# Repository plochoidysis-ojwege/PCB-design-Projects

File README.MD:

# PCB Design Projects

I created this repository to document my learning journey with KiCad and to share my designs with others. My goal is to create a comprehensive resource for anyone looking to get started with PCB design using KiCad and also as a personal reference for my future projects.
The structure of this repository is as follows:
1. [Learning and Desmistifying KiCad first directory](https://github.com/plochoidysis-ojwege/PCB-design-Projects/tree/main/Learning%20and%20desmistifyng%20KiCad%20first)  - here , I use tutorials and examples to learn the basics of KiCad and PCB design.
2. [My original designs directory](https://github.com/plochoidysis-ojwege/PCB-design-Projects/tree/main/My%20original%20designs) - here, I apply what I've learned in more advanced projects and explore additional features of KiCad.
3. [Documentation](https://github.com/plochoidysis-ojwege/PCB-design-Projects/tree/main/Documentation)-of essence, each project has its own documentation folder in its directory, so this directory has two files :
   - [Glossary of KiCad terms.md](https://github.com/plochoidysis-ojwege/PCB-design-Projects/blob/main/Documentation/Glossary%20of%20KiCad%20terms.MD) - here, I define key terms and concepts related to KiCad and PCB design.
   - [Important links.md](https://github.com/plochoidysis-ojwege/PCB-design-Projects/blob/main/Documentation/Important%20links.md) - here, I keep links to all the documentation related to my projects, including design notes, tutorials, and references, but of essence, each project has its own documentation folder in its directory.
   * Note that:
- Each project is contained within its own directory
- Each project directory includes the KiCad project files, as well as any relevant documentation
- The README.md file in each project directory provides an overview of the project and its goals.

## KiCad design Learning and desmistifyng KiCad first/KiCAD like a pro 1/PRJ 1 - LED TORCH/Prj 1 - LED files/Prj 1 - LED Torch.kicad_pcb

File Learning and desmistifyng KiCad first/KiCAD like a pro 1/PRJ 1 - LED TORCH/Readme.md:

# LED Torch Project
This is my first project using KiCad. The goal is to design a simple LED torch circuit and overally to learn the basics of KiCad, including schematic capture and PCB layout.
## Components
- 1 x LED
- 1 x Resistor
- 1 x  Battery
- 1 x Battery Clip
- 1 x Switch

## Schematic
Below is a simple schematic representation of the LED torch circuit:

From this schematic, I learnt the following features of KiCad:
- How to set up a new project and configure the environment(including grid settings)
- How to place components on the schematic
- How to wire components together
- How to annotate the schematic
- How to run electrical rules checks (ERC)

The problem and I still haven't figured out is whether the warning about the unplaced unit is something I need to address before moving on to the PCB layout.Is it that big deal. In this case , the sinlge pole switch had unplaced unit B as shown below :

but , it's the beginning and I have time to figure it out.

## PCB Layout
Below is the PCB layout for the LED torch circuit:

From this layout, I learnt the following features of KiCad:
- How to import the schematic into the PCB layout
- How to place components on the PCB
- How to route traces between components
- How to define board edges and cutouts
- How to run DRC(Design rules checks)
- How to generate [Gerber files](https://github.com/plochoidysis-ojwege/PCB-design-Projects/tree/main/Learning%20and%20desmistifyng%20KiCad%20first/KiCAD%20like%20a%20pro%201/PRJ%201%20-%20LED%20TORCH/Prj%201%20-%20LED%20%20files/Gerber%20files%20for%20this%20project) for manufacturing.
  
  Below is the design rules check;

The thing I found challenging was the routing process, especially ensuring that all traces were properly connected and that there were no unintentional shorts. Again here I realised their is a minimum distance between traces that I need to adhere to.

The PCB layout process was quite intuitive, and I appreciate the visual feedback KiCad provides while routing traces. I still need to learn more about design rules and how to ensure my layout is manufacturable, but I'm excited to continue this journey.
Below is a 3D view of the PCB layout:

Here is the back view;

I have included the files for this project -
[HERE](https://github.com/plochoidysis-ojwege/PCB-design-Projects/tree/main/Learning%20and%20desmistifyng%20KiCad%20first/KiCAD%20like%20a%20pro%201/PRJ%201%20-%20LED%20TORCH/Prj%201%20-%20LED%20%20files)

---
THE END

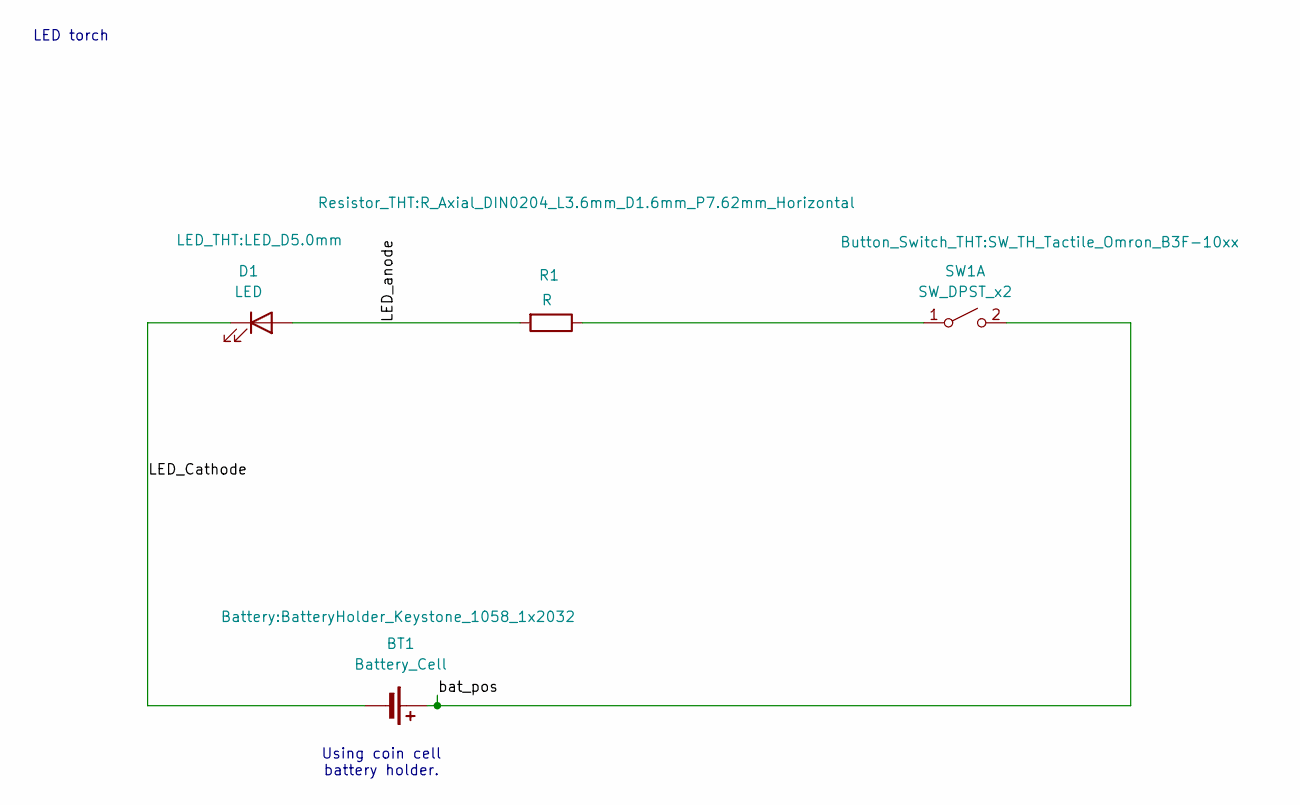
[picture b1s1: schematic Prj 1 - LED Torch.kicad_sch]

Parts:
BT1: Battery_Cell; BatteryHolder_Keystone_1058_1x2032
D1: LED; LED_D5.0mm
R1: R; R_Axial_DIN0204_L3.6mm_D1.6mm_P7.62mm_Horizontal
SW1: SW_DPST_x2; SW_TH_Tactile_Omron_B3F-10xx

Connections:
/LED_Cathode: BT1.2 (-), D1.1 (K)
/LED_anode: D1.2 (A), R1.2
/bat_pos: BT1.1 (+), SW1.2 (B)
unnamed: R1.1, SW1.1 (A)

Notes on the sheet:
Using coin cell battery holder.
LED torch

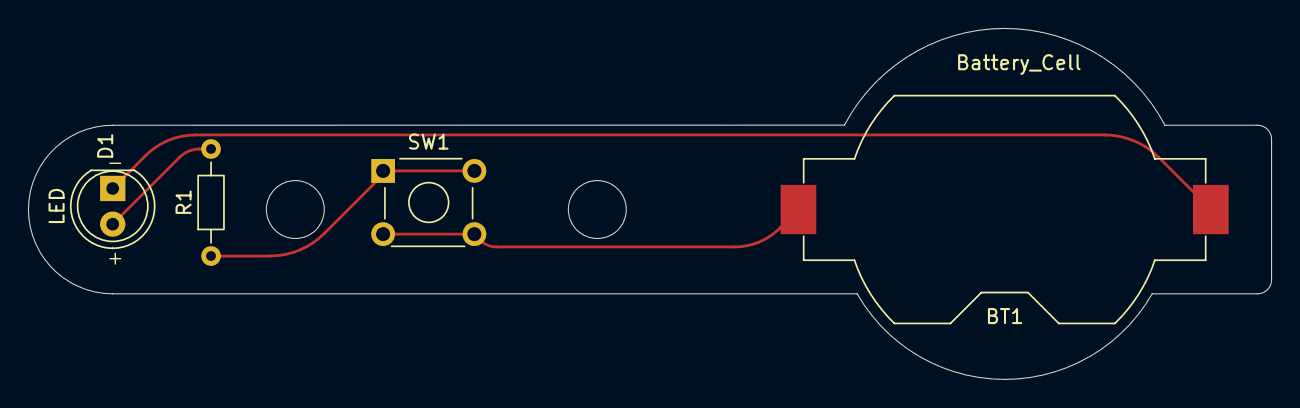
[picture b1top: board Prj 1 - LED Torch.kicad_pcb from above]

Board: 2 copper layers, 88.5 x 25.0 mm, 5 parts (1 on the bottom side), 4 nets.

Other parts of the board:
REF1: KiCad-Logo2_8mm_SilkScreen

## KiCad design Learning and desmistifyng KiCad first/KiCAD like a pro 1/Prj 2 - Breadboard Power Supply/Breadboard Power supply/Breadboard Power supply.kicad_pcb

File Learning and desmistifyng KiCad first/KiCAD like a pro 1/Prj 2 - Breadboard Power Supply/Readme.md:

# Breadboard Power supply
## Overview
This is the second project I've done.It was inspired by the project in the book "Kicad like a pro" by Peter Dalmaris under a chapter called "Part 9:Project-Design a simple breadboard power supply PCB".This was a project to design a simple breadboard power supply PCB,to provide power to circuits implemented on a mini breadboard, which is a core part of electronics prototyping.The inspiration for the design of the PCB came from creating small eletronics for his(Peter Dalmaris') Arduino and ESP32 courses. When the circuit he was building on the breadboard needed more power than the MCU could provide, he settled on this project.

 For the breadboard power supply,we needed something that:
 1. Plugs directly on the breadboard;therefore, there are no wires.
 2. Have an on/off switch.
 3. Can provide 5V and 3.3V power.
 4. Can draw power from a range of wall power supplies,from 6V to 12V.

 The breadboard connects to the PCB through two sets of pin headers.Two double screw terminals are added to provide additional way to output power via jumper wires instead pins.

 From this project I learnt the following: 
 - How to import and use footprints and parts from external libraries.
 - How to use vias in routing to connect the B.copper to F.copper routes.
 - How to use copper fills and their importance.

 And other things, I already learnt them in other subsequent projects or I'm yet to.
 ## Bill of Materials
 Here is the generated B.O.M
 
 This was not the bill of materials used in KiCad like a pro,I used my own switch instead of the digikey one used in the book.And also assigned a footprint that is compartible as you can see.
## Schematic
Here is the schematic design, from it ,you can infer the bill of materials:

As you can see,I was unable to use the parts and footprints from the digikey library as used in the Peter's book.But still Im working on that, I'll update the next version.For that reason , this repository has two branches ,the main branch just for the projects as I did them, which may include things I couldnt figure out , and then the master branch containing the corrected versions of the projects.

I made sure the Electrical Rules Check was clean:-[ERC](https://github.com/plochoidysis-ojwege/PCB-design-Projects/blob/main/Learning%20and%20desmistifyng%20KiCad%20first/KiCAD%20like%20a%20pro%201/Prj%202%20-%20Breadboard%20Power%20Supply/Breadboard%20Power%20supply/ERC.rpt)

 ## PCB Layout 
 At this stage,I learnt a lot and used some of the features for the first time.To me , this is the most crucial part of the PCB design.I learnt the following;
 - Using vias for the first time to connect the F.copper and the B.copper routes where routing was not possible due to routes on same copper layer having to cross over each other.
 - Using the "lock" feature helped me to avoid unnecessarily moving a footprints to ensure accuracy and precision.In this case , the distance between J6 and J4 needs to fixed during this whole entire process.I only unlocked after the whole process.
 - How to use copper fills and their importance.I created a 
copper fill in the bottom copper layer and connected it to the GND net.This resulted in a fully routed board. Even though I had fully routed the footprints including the grounds , even if I  didn't route the grounds, using copper fills and connecting it to the GND generally results into a fully routed board.
---
Below is the PCB Layout;
This is how it looked before the copper fills , you can see I used the vias.

---
The bottom view ,the vias makes it easier to connect the two routes as you can see.

---
The copper fill is so important, here I connected it with the GND net, the board was complete as shown;

.png)
 And in 3D ;

 And I made sure the Design Rules check was clean. You can check it here
 [DRC](https://github.com/plochoidysis-ojwege/PCB-design-Projects/blob/main/Learning%20and%20desmistifyng%20KiCad%20first/KiCAD%20like%20a%20pro%201/Prj%202%20-%20Breadboard%20Power%20Supply/Breadboard%20Power%20supply/DRC.rpt)

 ---
 This project was mainly for learning new things and I did.
 I have included the files for this project in this directory-

[Here](https://github.com/plochoidysis-ojwege/PCB-design-Projects/tree/main/Learning%20and%20desmistifyng%20KiCad%20first/KiCAD%20like%20a%20pro%201/Prj%202%20-%20Breadboard%20Power%20Supply/Breadboard%20Power%20supply)

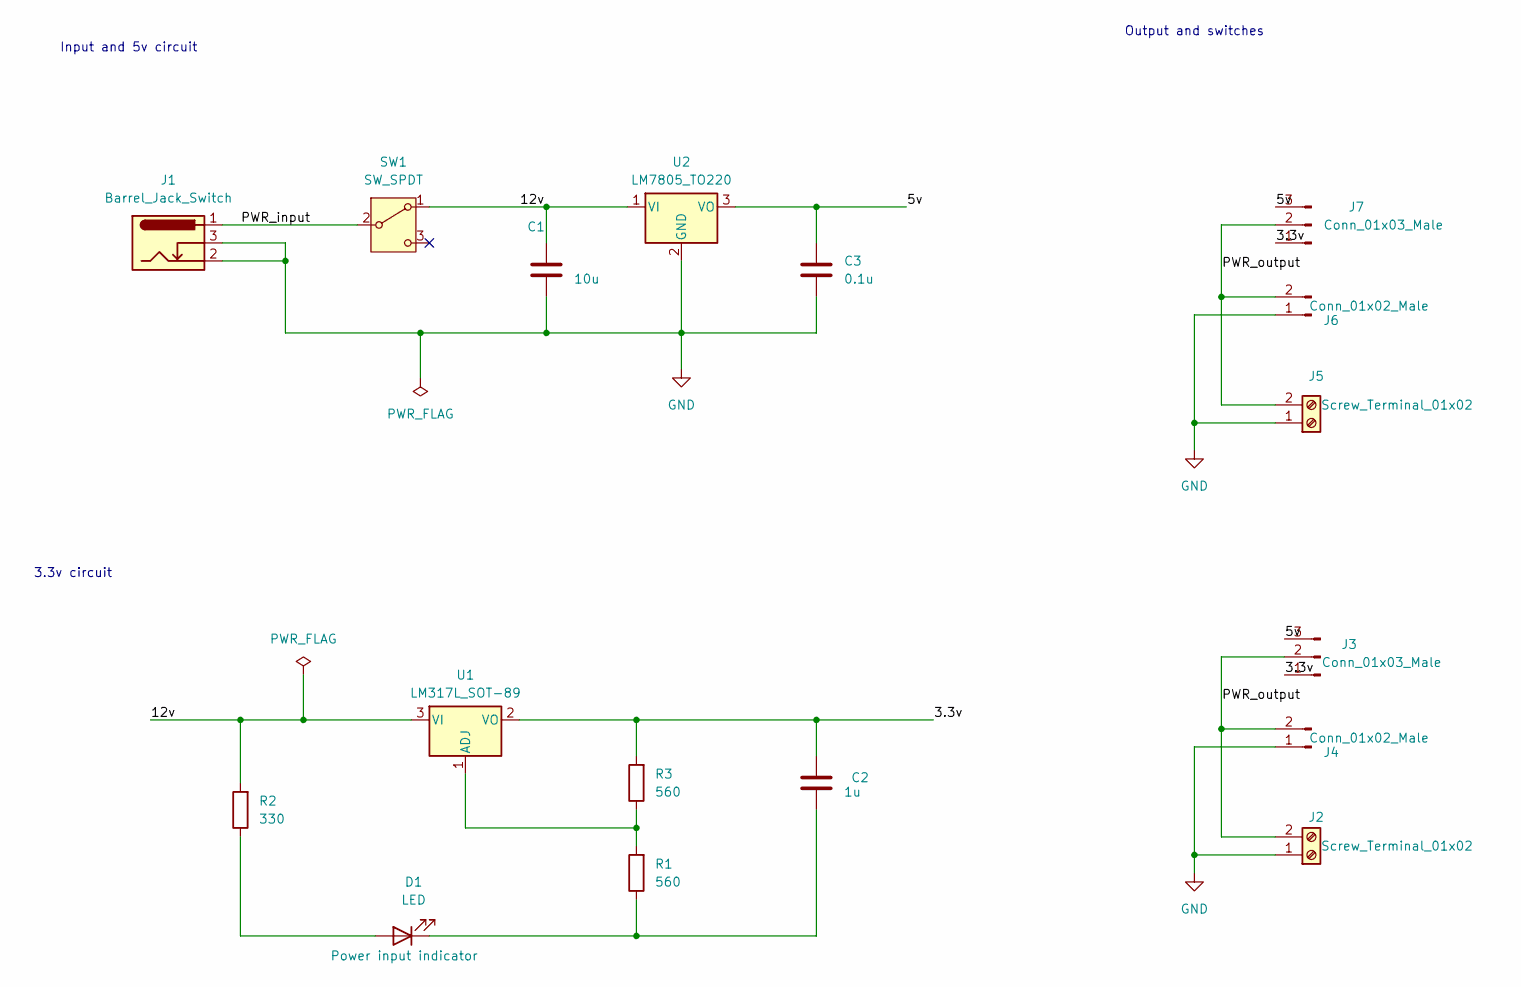
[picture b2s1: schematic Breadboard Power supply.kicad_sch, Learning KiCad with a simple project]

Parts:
C1: 10u; C_Disc_D3.0mm_W1.6mm_P2.50mm
C2: 1u; C_Disc_D3.0mm_W1.6mm_P2.50mm
C3: 0.1u; C_Disc_D3.0mm_W1.6mm_P2.50mm
D1: LED; LED_D5.0mm
J1: Barrel_Jack_Switch; BarrelJack_Horizontal
J2, J5: Screw_Terminal_01x02; TerminalBlock_bornier-2_P5.08mm
J3, J7: Conn_01x03_Male; PinHeader_1x03_P2.54mm_Vertical
J4, J6: Conn_01x02_Male; PinHeader_1x02_P2.54mm_Vertical
R1, R3: 560; R_Axial_DIN0204_L3.6mm_D1.6mm_P7.62mm_Horizontal
R2: 330; R_Axial_DIN0204_L3.6mm_D1.6mm_P7.62mm_Horizontal
SW1: SW_SPDT; SW_Slide-03_Wuerth-WS-SLTV_10x2.5x6.4_P2.54mm
U1: LM317L_SOT-89; SOT-89-3
U2: LM7805_TO220; TO-220-3_Vertical

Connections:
/3.3v: C2.1, J3.1, J7.1, R3.2, U1.2 (VO)
/5v: C3.1, J3.3, J7.3, U2.3 (VO)
/12v: C1.1, R2.2, SW1.1 (A), U1.3 (VI), U2.1 (VI)
/PWR_input: J1.1, SW1.2 (B)
/PWR_output: J2.2, J3.2, J4.2, J5.2, J6.2, J7.2
GND: C1.2, C3.2, J1.2, J1.3, J2.1, J4.1, J5.1, J6.1, U2.2 (GND)
unnamed: D1.2 (A), R2.1
unnamed: C2.2, D1.1 (K), R1.1
unnamed: R1.2, R3.1, U1.1 (ADJ)

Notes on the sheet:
Output and switches
3.3v circuit
Input and 5v circuit

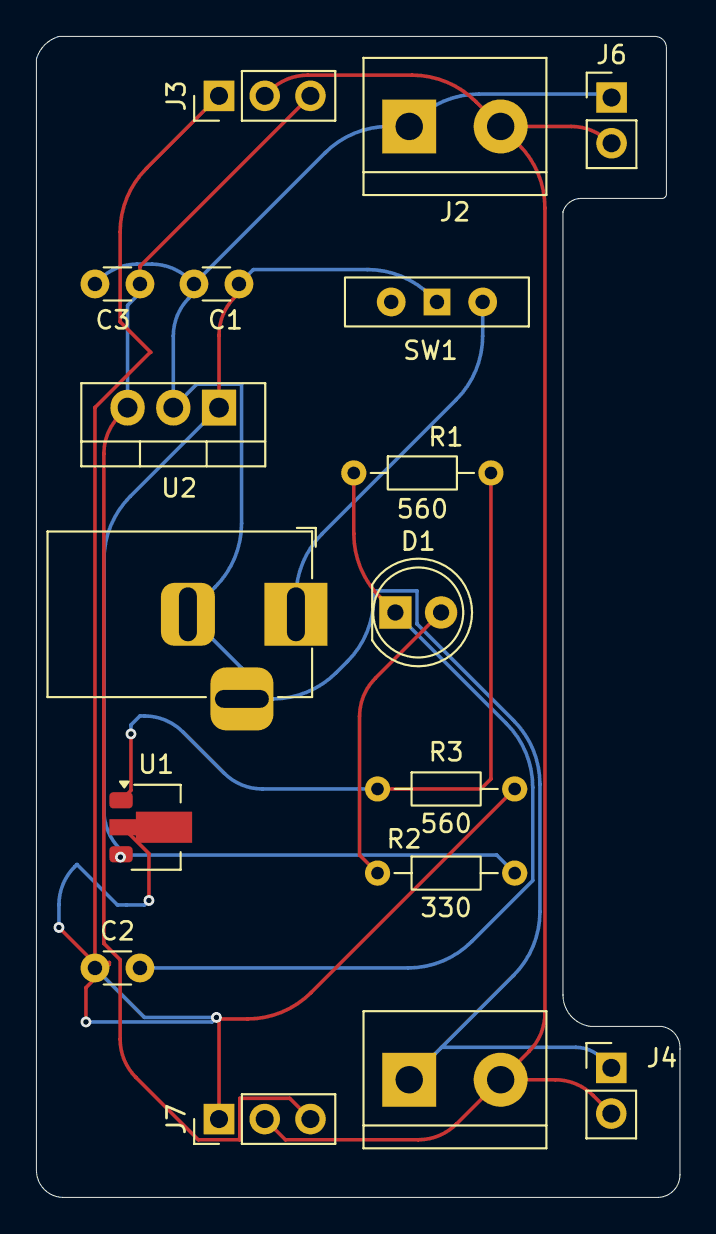
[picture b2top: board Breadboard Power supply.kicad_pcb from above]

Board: 2 copper layers, 35.8 x 64.5 mm, 17 parts (0 on the bottom side), 9 nets.

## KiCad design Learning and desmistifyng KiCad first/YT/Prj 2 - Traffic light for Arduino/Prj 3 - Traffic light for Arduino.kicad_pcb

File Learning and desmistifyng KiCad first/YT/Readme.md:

# YT
These are obviously , the tutorials that helped me from youtube and in this directory are designs I made following those tutorials.

## They include
- Project 1 [Design ESP 32](https://github.com/plochoidysis-ojwege/PCB-design-Projects/tree/main/Learning%20and%20desmistifyng%20KiCad%20first/YT/Prj%201%20-%20DesignESP32%20S%203)
- Project 2 [Advanced KiCad Techniques](https://www.youtube.com/playlist?list=PL1A2B3C4D5E6F7G8H9I0K)
- Project 3 [Design and Assembly of ESP32](https://github.com/plochoidysis-ojwege/PCB-design-Projects/tree/main/Learning%20and%20desmistifyng%20KiCad%20first/YT/Prj%203-KiCad%209%20Design%20%26%20assemble%20an%20ESP32%20IoT%204-layer%20PCB%20loaded%20with%20goodies)
- Project 4 [EEVblog](https://www.youtube.com/user/EEVblog)

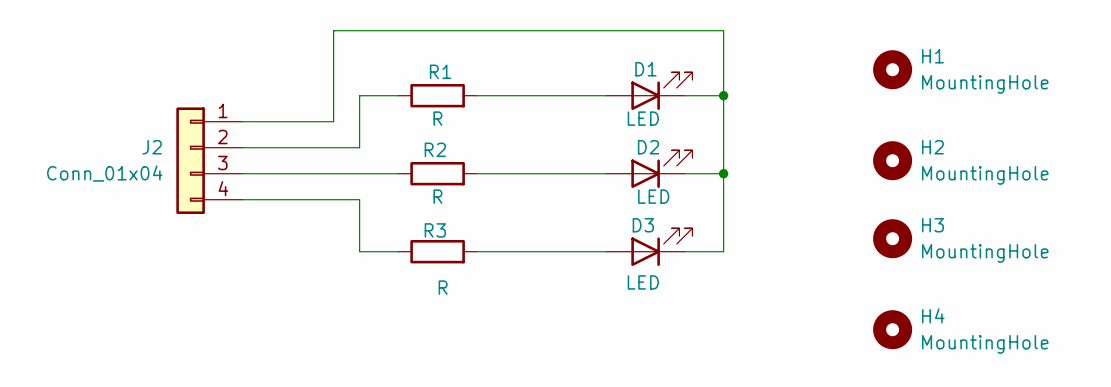
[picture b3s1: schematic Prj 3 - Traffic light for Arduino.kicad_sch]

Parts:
D1, D2, D3: LED; LED_D3.0mm
H1, H2, H3, H4: MountingHole; MountingHole_2.5mm_Pad
J2: Conn_01x04; PinHeader_1x04_P2.54mm_Horizontal
R1, R2, R3: R; R_Axial_DIN0204_L3.6mm_D1.6mm_P5.08mm_Horizontal

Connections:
unnamed: D1.2 (A), R1.2
unnamed: D1.1 (K), D2.1 (K), D3.1 (K), J2.1
unnamed: D2.2 (A), R2.2
unnamed: D3.2 (A), R3.2
unnamed: J2.2, R1.1
unnamed: J2.3, R2.1
unnamed: J2.4, R3.1

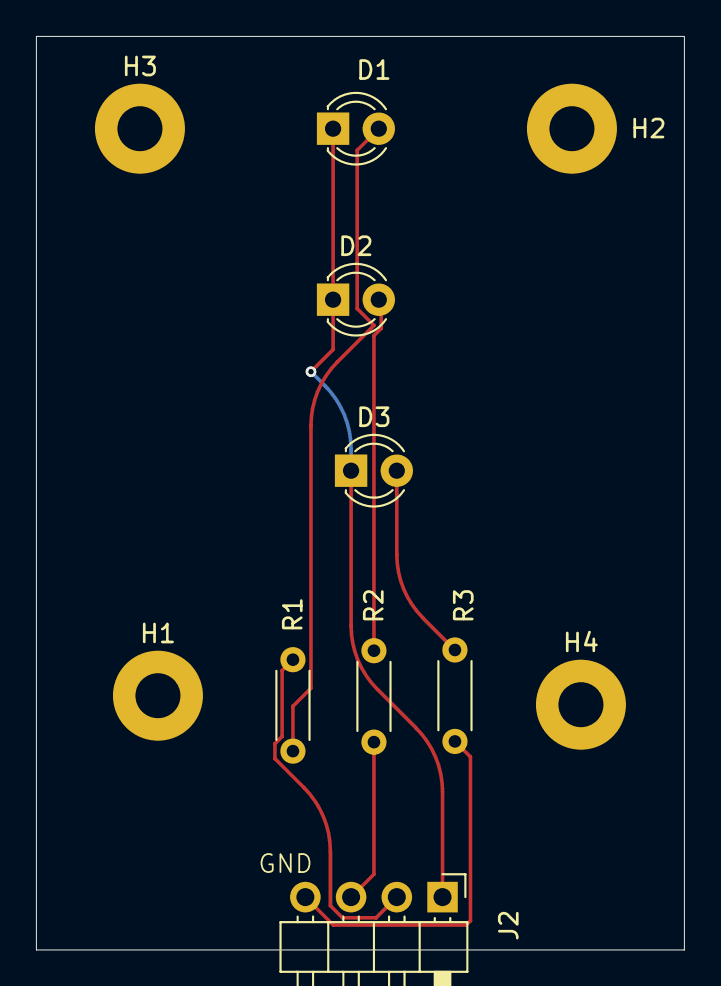
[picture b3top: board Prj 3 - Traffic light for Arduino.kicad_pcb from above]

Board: 2 copper layers, 36.0 x 50.8 mm, 11 parts (0 on the bottom side), 7 nets.

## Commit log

2025-08-23 Initial commit of PCB design projects
2025-08-23 Create Apache License
2025-08-23 update documentation
2025-09-11 add a new project-design and assembly of an esp32
2025-09-18 Update important links and add new projects
2025-09-22 update the schematic for the breadboard power supply
2025-09-27 update libraries and The breadboard power supply
2025-09-29 update breadboard power supply project
2025-10-02 update the breadboard power supply files
2025-10-05 updates on demistifying kicad
2025-10-05 pcb 3d after hatch
2025-10-07 update BOM
2025-11-17 add updates
